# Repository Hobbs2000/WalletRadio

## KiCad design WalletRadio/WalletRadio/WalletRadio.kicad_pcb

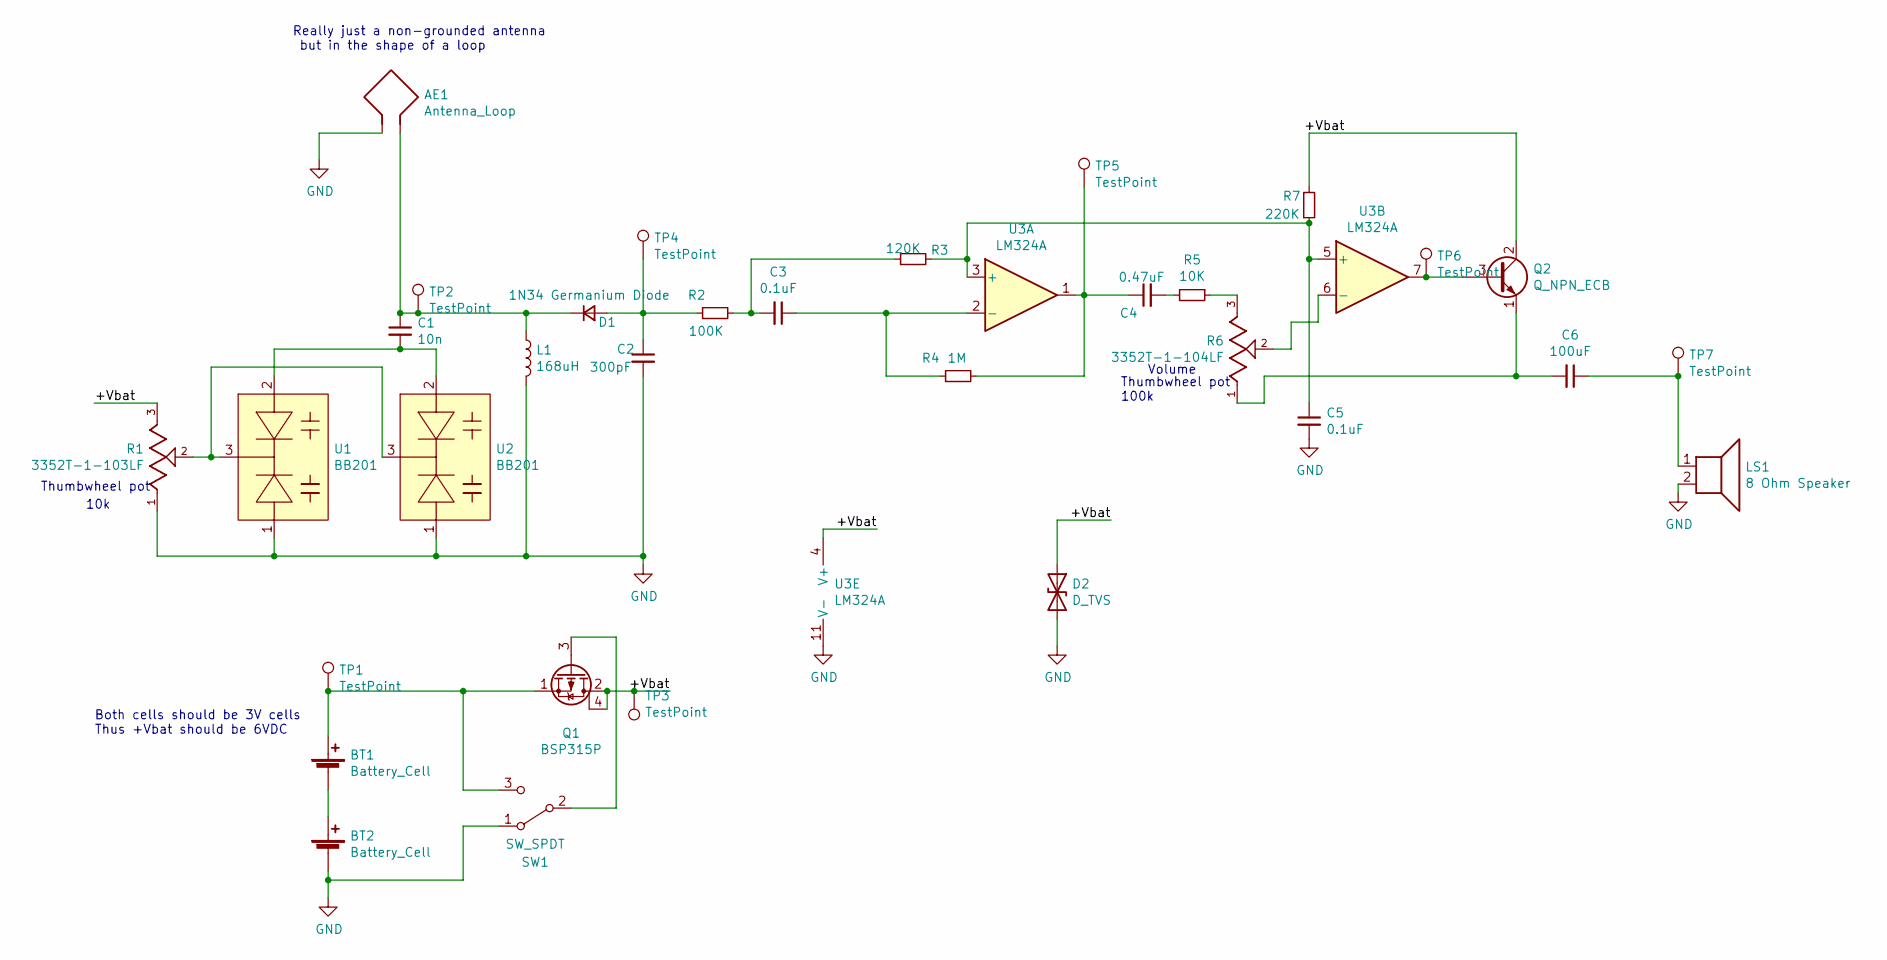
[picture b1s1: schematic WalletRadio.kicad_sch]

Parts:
AE1: Antenna_Loop; Loop_Antenna
BT1, BT2: Battery_Cell; 20mmCoinCell
C1: 10n; C_0603_1608Metric_Pad1.08x0.95mm_HandSolder
C2: 300pF; C_0603_1608Metric_Pad1.05x0.95mm_HandSolder
C3, C5: 0.1uF; C_0603_1608Metric_Pad1.05x0.95mm_HandSolder
C4: 0.47uF; C_0603_1608Metric_Pad1.05x0.95mm_HandSolder
C6: 100uF; R_0603_1608Metric_Pad1.05x0.95mm_HandSolder
D1: 1N34 Germanium Diode; SOT-323_SC-70_Handsoldering
D2: D_TVS; 5.0SMDJ9.0CA
L1: 168uH; PE-53828NL
LS1: 8 Ohm Speaker; Wall
Q1: BSP315P; SOT-223
Q2: Q_NPN_ECB; SOT-89-3_Handsoldering
R1: 3352T-1-103LF; TRIM_3352T-1-103LF; PARTREV 08/19
R2: 100K; R_0603_1608Metric_Pad1.05x0.95mm_HandSolder
R3: 120K; R_0603_1608Metric_Pad1.05x0.95mm_HandSolder
R4: 1M; R_0603_1608Metric_Pad1.05x0.95mm_HandSolder
R5: 10K; R_0603_1608Metric_Pad1.05x0.95mm_HandSolder
R6: 3352T-1-104LF; TRIM_3352T-1-103LF; PARTREV 08/19
R7: 220K; R_0603_1608Metric_Pad1.05x0.95mm_HandSolder
SW1: SW_SPDT; CUS-12TB_Switch
TP1, TP2, TP3, TP4, TP5, TP6, TP7: TestPoint; TestPoint_Pad_1.5x1.5mm
U1, U2: BB201; SOT-23_Handsoldering
U3: LM324A; SOIC-14_3.9x8.7mm_P1.27mm

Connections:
/+Vbat: D2.1 (A1), Q1.2 (D), Q1.4 (D), Q2.2 (C), R1.3, R7.1, TP3.1, U3.4 (V+)
GND: AE1.1, BT2.2 (-), C2.2, C5.2, D2.2 (A2), L1.2, LS1.2, R1.1, SW1.1 (A), U1.1, U2.1, U3.11 (V-)
unnamed: AE1.2, C1.1, D1.1 (K), L1.1, TP2.1
unnamed: BT1.1 (+), Q1.1 (S), SW1.3 (C), TP1.1
unnamed: BT1.2 (-), BT2.1 (+)
unnamed: C1.2, U1.2, U2.2
unnamed: C2.1, D1.2 (A), R2.1, TP4.1
unnamed: C3.1, R4.1, U3.2 (-)
unnamed: C3.2, R2.2, R3.1
unnamed: C4.1, R4.2, TP5.1, U3.1
unnamed: C4.2, R5.2
unnamed: C5.1, R3.2, R7.2, U3.3 (+), U3.5 (+)
unnamed: C6.1, LS1.1, TP7.1
unnamed: C6.2, Q2.1 (E), R6.1
unnamed: Q1.3 (G), SW1.2 (B)
unnamed: Q2.3 (B), TP6.1, U3.7
unnamed: R1.2, U1.3, U2.3
unnamed: R5.1, R6.3
unnamed: R6.2, U3.6 (-)

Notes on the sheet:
Both cells should be 3V cells Thus +Vbat should be 6VDC
Thumbwheel pot
Volume
10k
Really just a non-grounded antenna but in the shape of a loop
Thumbwheel pot 100k

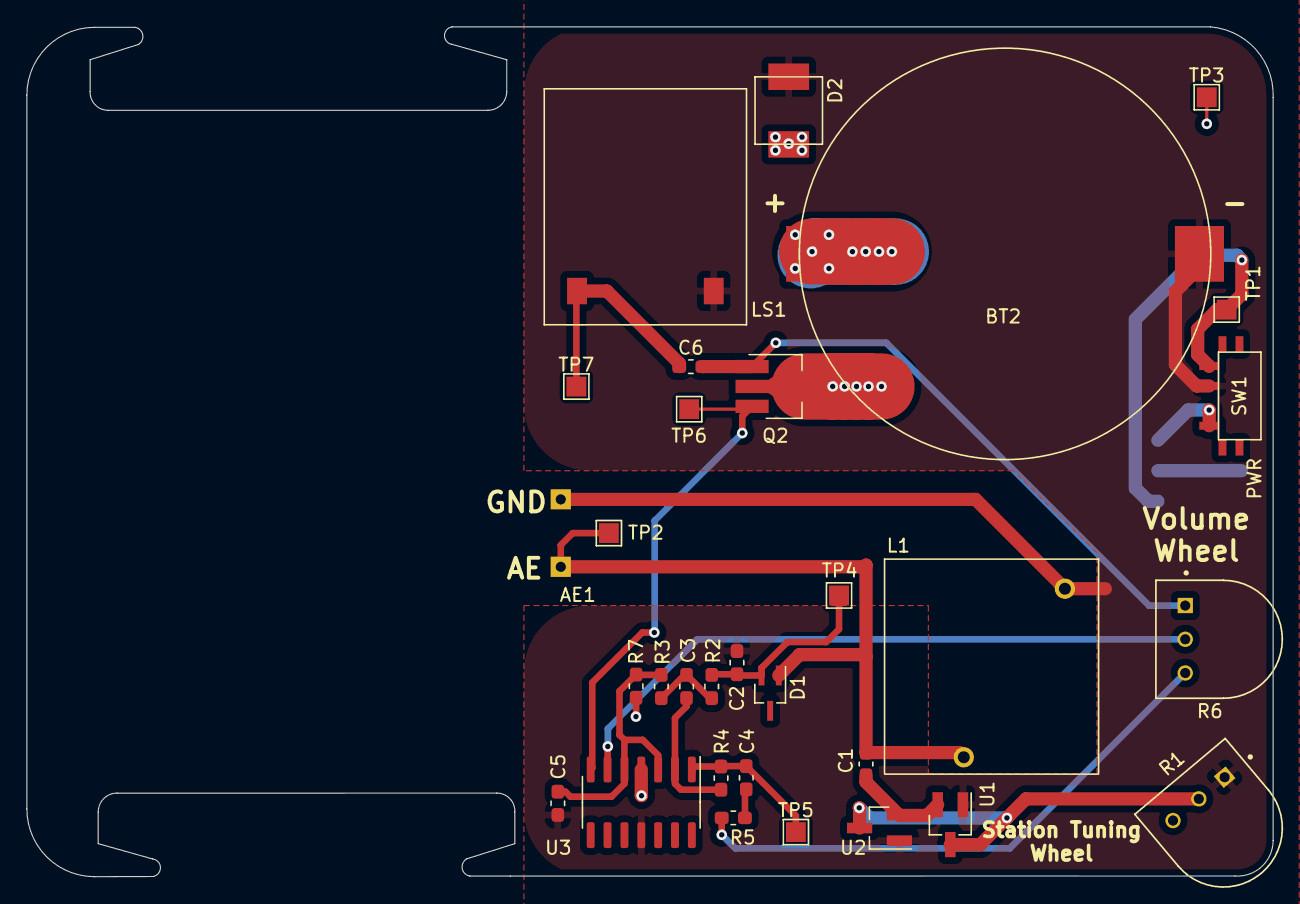
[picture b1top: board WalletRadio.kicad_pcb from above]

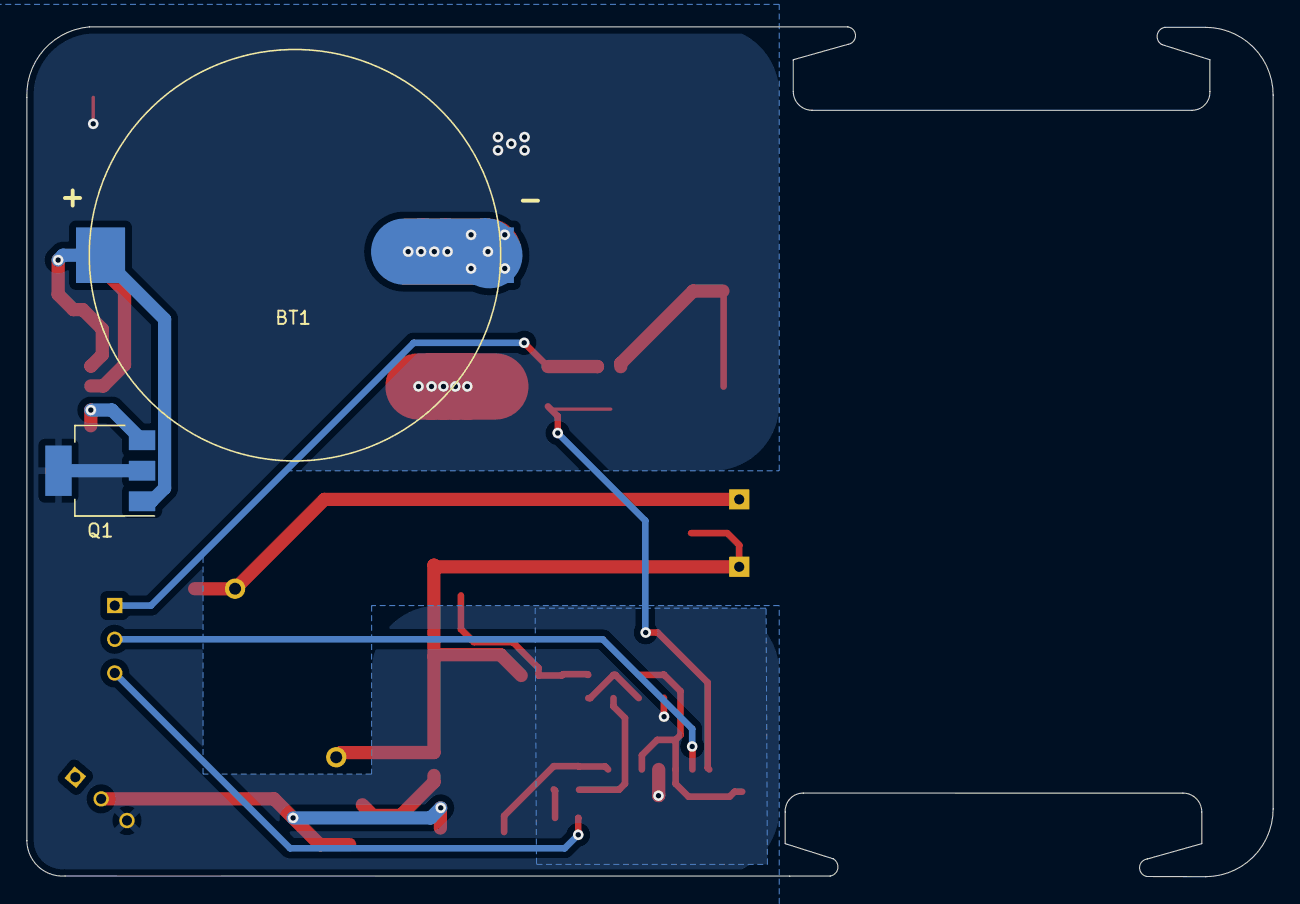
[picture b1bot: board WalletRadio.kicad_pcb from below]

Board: 2 copper layers, 93.9 x 64.0 mm, 33 parts (2 on the bottom side), 19 nets.

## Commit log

2022-01-28 Changed the tank circuit to use a varacter diode
2022-02-01 Swapped out several parts and did some rerouting
2022-02-01 Changed to KiCad 6.0
2022-02-01 Working on PCB antenna
2022-02-02 More embedded antenna work
2022-02-02 Slight edits to PCB
2022-02-03 Edited power switch, cleaned up layout
